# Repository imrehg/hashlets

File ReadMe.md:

# Hashlets for other hardware

Hashlet is a secure authentication device, and a cryptographic provider, designed to fit
easily on single-board computers. It's based on the [Atmel ATSHA204A][atmel] module.

Here are some remixed versions of the [original Hashlet by Cryptotronix][original]
for other hardware that are not covered by them.

## Hardware targets

* [VIA VAB-600 Springboard][springboard] through onboard headers (in progress)
* [VIA VAB-820][vab820] through onboard headers (planned)
* half-sized mini-PCIe card format for general embedded computing (planned)

For Raspberry Pi or BeagleBone Black versions (and possibly more!), see
[their Tindie store][cryptotronixstore]!

## Design

Designed with [KiCad][kicad] for open access, in the spirit of open source.

## License

The original Hashlet is under [CC-BY-SA-3.0][cc], so this is like that too!

[atmel]: http://www.atmel.com/devices/ATSHA204A.aspx "Atmel ATSHA204 product page"
[original]: https://github.com/cryptotronix/hashlet "GitHub repo for cryptotronix/hashlet"
[springboard]: http://www.viaspringboard.com "VIA Springboard homepage"
[vab820]: http://www.viaembedded.com/en/products/boards/2150/1/VAB-820_(Pico-ITX).html "VAB-820 homepage"
[cryptotronixstore]: https://www.tindie.com/products/cryptotronix/hashlet/
[kicad]: http://www.kicad-pcb.org/ "KiCad homepage"
[cc]: https://creativecommons.org/licenses/by-sa/3.0/ "Creative Commons Attribution-ShareAlike 3.0 Unported"

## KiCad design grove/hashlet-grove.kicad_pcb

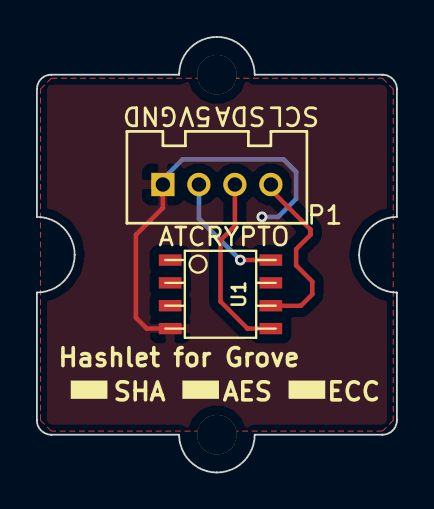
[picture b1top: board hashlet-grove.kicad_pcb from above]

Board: 2 copper layers, 20.0 x 24.2 mm, 4 parts (0 on the bottom side), 4 nets.

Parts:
HoleA: P***; 1pin
HoleB: P***; 1pin
P1: TWIG_2.0
U1: ATCRYPTO; so-8

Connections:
/SCL: P1.4, U1.6
/SDA: P1.3, U1.5
/VCC: P1.2, U1.8
GND: P1.1, U1.4

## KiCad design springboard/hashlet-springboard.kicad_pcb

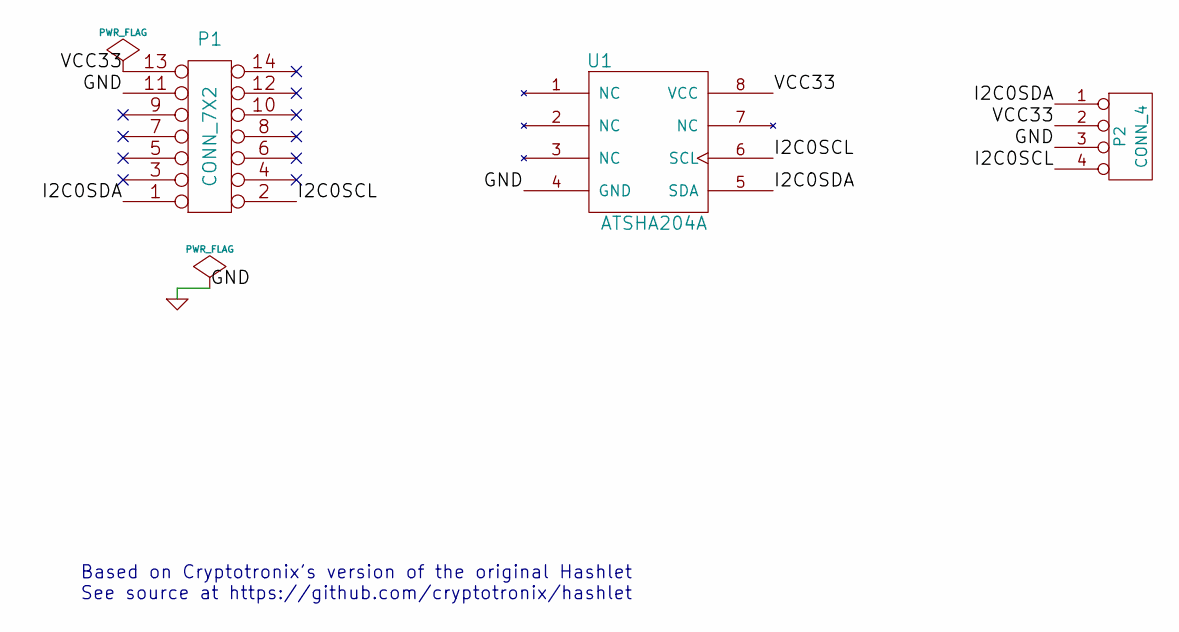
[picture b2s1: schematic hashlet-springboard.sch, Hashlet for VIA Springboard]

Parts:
P1: CONN_7X2
P2: CONN_4
U1: ATSHA204A

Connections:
/I2C0SCL: P1.2, P2.4, U1.6 (SCL)
/I2C0SDA: P1.1, P2.1, U1.5 (SDA)
/VCC33: P1.13, P2.2, U1.8 (VCC)
GND: P1.11, P2.3, U1.4 (GND)

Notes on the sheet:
Based on Cryptotronix's version of the original Hashlet See source at https://github.com/cryptotronix/hashlet

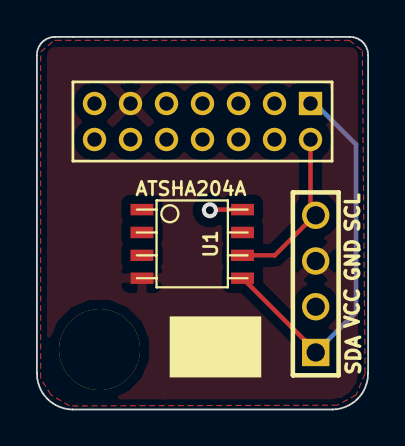
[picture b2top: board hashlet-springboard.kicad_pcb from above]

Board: 2 copper layers, 18.4 x 20.7 mm, 4 parts (0 on the bottom side), 4 nets.

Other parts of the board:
PIN_ARRAY_1: Val**; PIN_ARRAY_1

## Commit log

2014-11-16 Hashlet for Springboard: work in progress
2014-11-16 add Readme
2014-12-09 springboard: PCB preparation v1
2014-12-10 springboard: adjusted wiring before submission to manufacturing
2014-12-10 springboard: add Gerber files
2014-12-19 fix typo in directory name
2015-08-09 Work in progress: Hashlet for Grove
2015-08-15 Hashlet for Grove rev v1
2015-08-16 board updated before manufacturing
